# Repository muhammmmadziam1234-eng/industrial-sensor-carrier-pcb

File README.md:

# Meridian Industrial Sensor Carrier · Revision B

Meridian is a four-layer PCB design for integrating a 3.3 V controller with RS-485, SPI, I²C, analog sensing, and low-side loads. Revision B adds a hardware supply selector, wider power routes, dedicated inner copper planes, and an editable schematic and layout tied to the same pin map.

[View all four copper layers](media/four-layer-inspection.png)

| Deliverable | Contents |
| --- | --- |
| [KiCad project](cad/meridian-carrier.kicad_pro) | Native schematic, PCB, project symbol and footprint libraries, and explicit routing constraints. |
| [Schematic PDF](reports/meridian-schematic.pdf) | Review drawing organized by electrical function. |
| [AutoCAD DXF](cad/meridian-carrier.dxf) | Millimetre model with board outline, mounting, drills, individual tracks, and separately editable inner plane models. |
| [Mechanical STEP](cad/meridian-carrier-board.step) | Board solid for enclosure fit, with mounting bores checked against the nonplated drill output. |
| [Assembly and purchasing](cad/bill-of-materials.csv) | Reference designators, package details, candidate manufacturer part numbers, and source links. |
| [Connector and jumper map](design-review.md) | Controller pinout, field connectors, power selection, and test points. |
| [Engineering basis](engineering-basis.md) | Component and fabrication references, electrical decisions, and the integration envelope. |
| [Fabrication review](fab/README.md) | Stack, drill, copper, and manufacturing checks for the prototype package. |
| [First-article acceptance](first-article.md) | Bench setup, measurable acceptance criteria, and evidence to collect. |

The board measures 101.60 × 76.20 mm and uses four 3.20 mm mounting holes. L2 provides a ground plane and L3 provides the 3.3 V plane. The two outer layers carry signal and power tracks. JP3 selects the controller supply or a regulated auxiliary input with a single shunt.

## Verify and regenerate

Install the Python dependencies in [requirements.txt](requirements.txt). Run the generators from the project root in this order.

~~~sh
python schematic.py
python route.py
python verify.py
python check_verifier.py
python planes.py
python export_cad.py
python render_preview.py
~~~

[Geometry evidence](verification.json) covers the routed copper, hole spacing, board edge, and connectivity. [Plane evidence](plane-verification.json) covers continuous inner pours and their isolation envelopes. [Export evidence](cad/export-checks.json) records the DXF audit and KiCad geometry readback. [KiCad 10.0.8 results](reports/native-summary.json) record zero electrical or layout findings, zero unconnected items, zero schematic parity issues, and agreement on all 124 electrical pad assignments. The [fabrication export check](reports/fabrication-summary.json) confirms nine Gerber layers, 117 plated and four nonplated drill hits, and 23 top-side surface-mount placements. See [the fabrication folder](fab/README.md) for export instructions and the file manifest.

[Mechanical readback](reports/mechanical-summary.json) compares the STEP solid with the board dimensions and all four mounting bores in the nonplated drill output. The STEP is for fit review and excludes fitted components. Its exported Z span reflects the KiCad model. Use the fabricator-approved stack and component heights to set actual enclosure clearances.

This handoff is for engineering and prototype review. Fabrication approval requires final part-to-footprint confirmation and review of the chosen fab stack. Hardware validation uses the documented bring-up plan.

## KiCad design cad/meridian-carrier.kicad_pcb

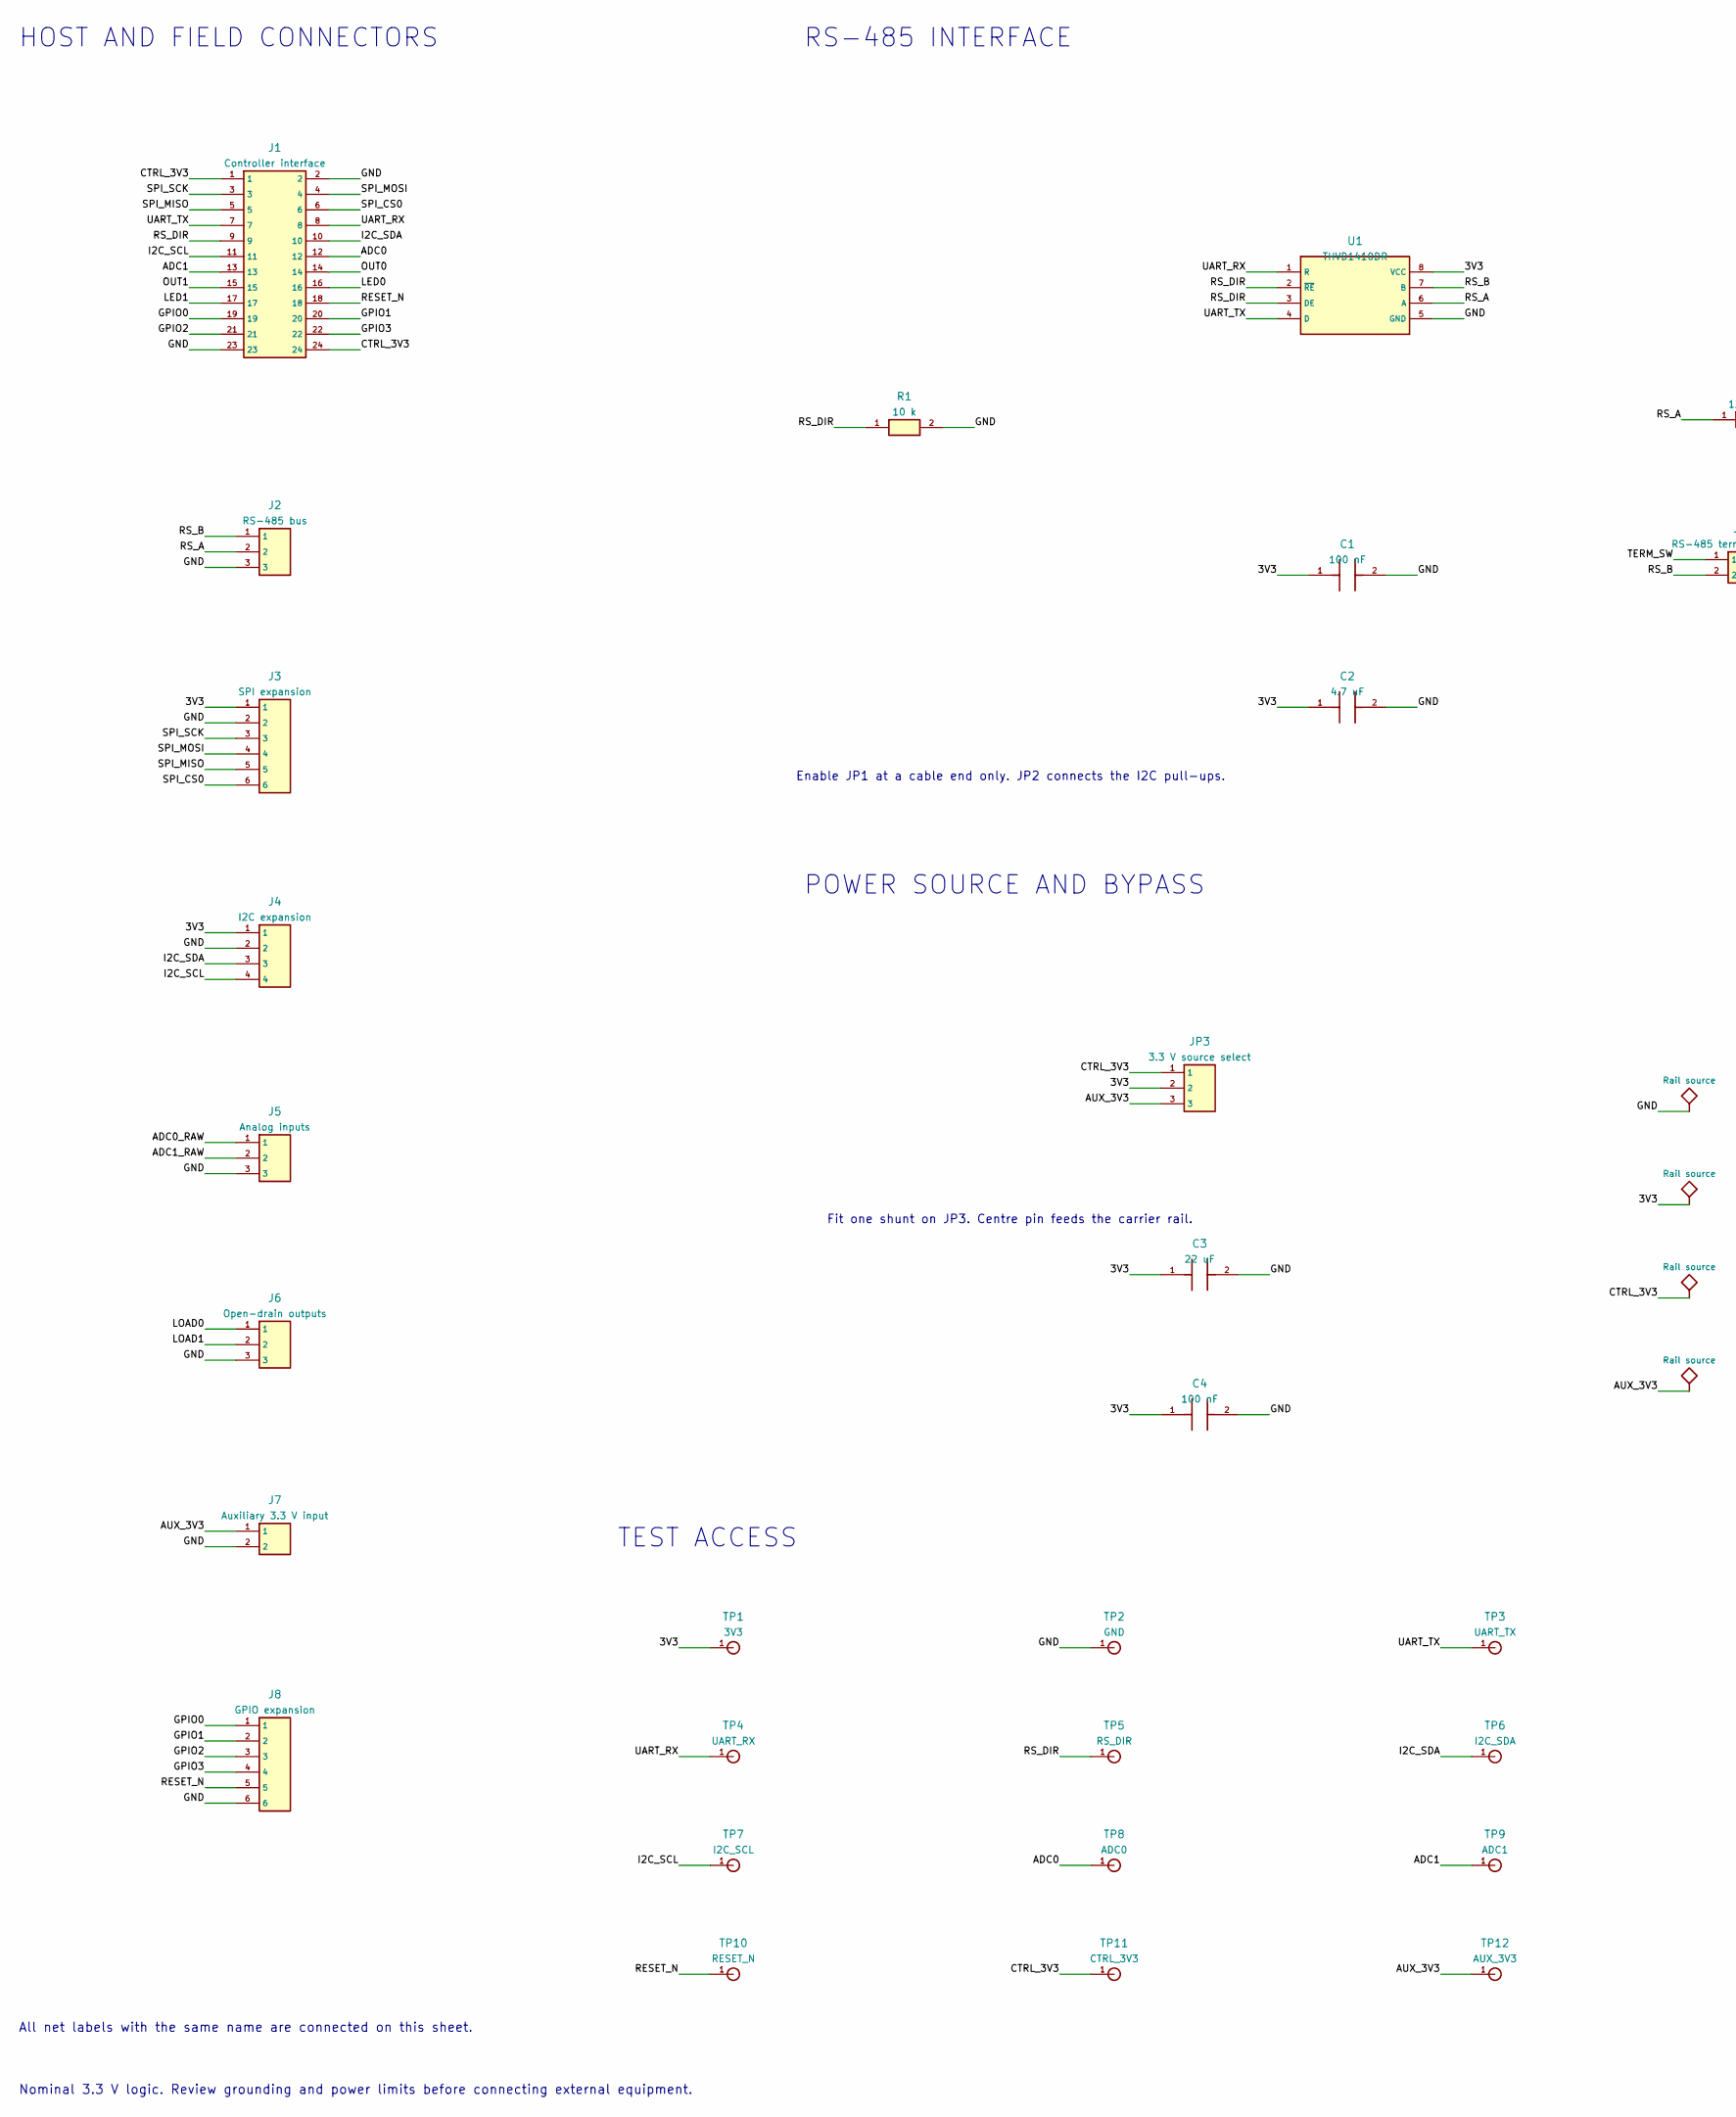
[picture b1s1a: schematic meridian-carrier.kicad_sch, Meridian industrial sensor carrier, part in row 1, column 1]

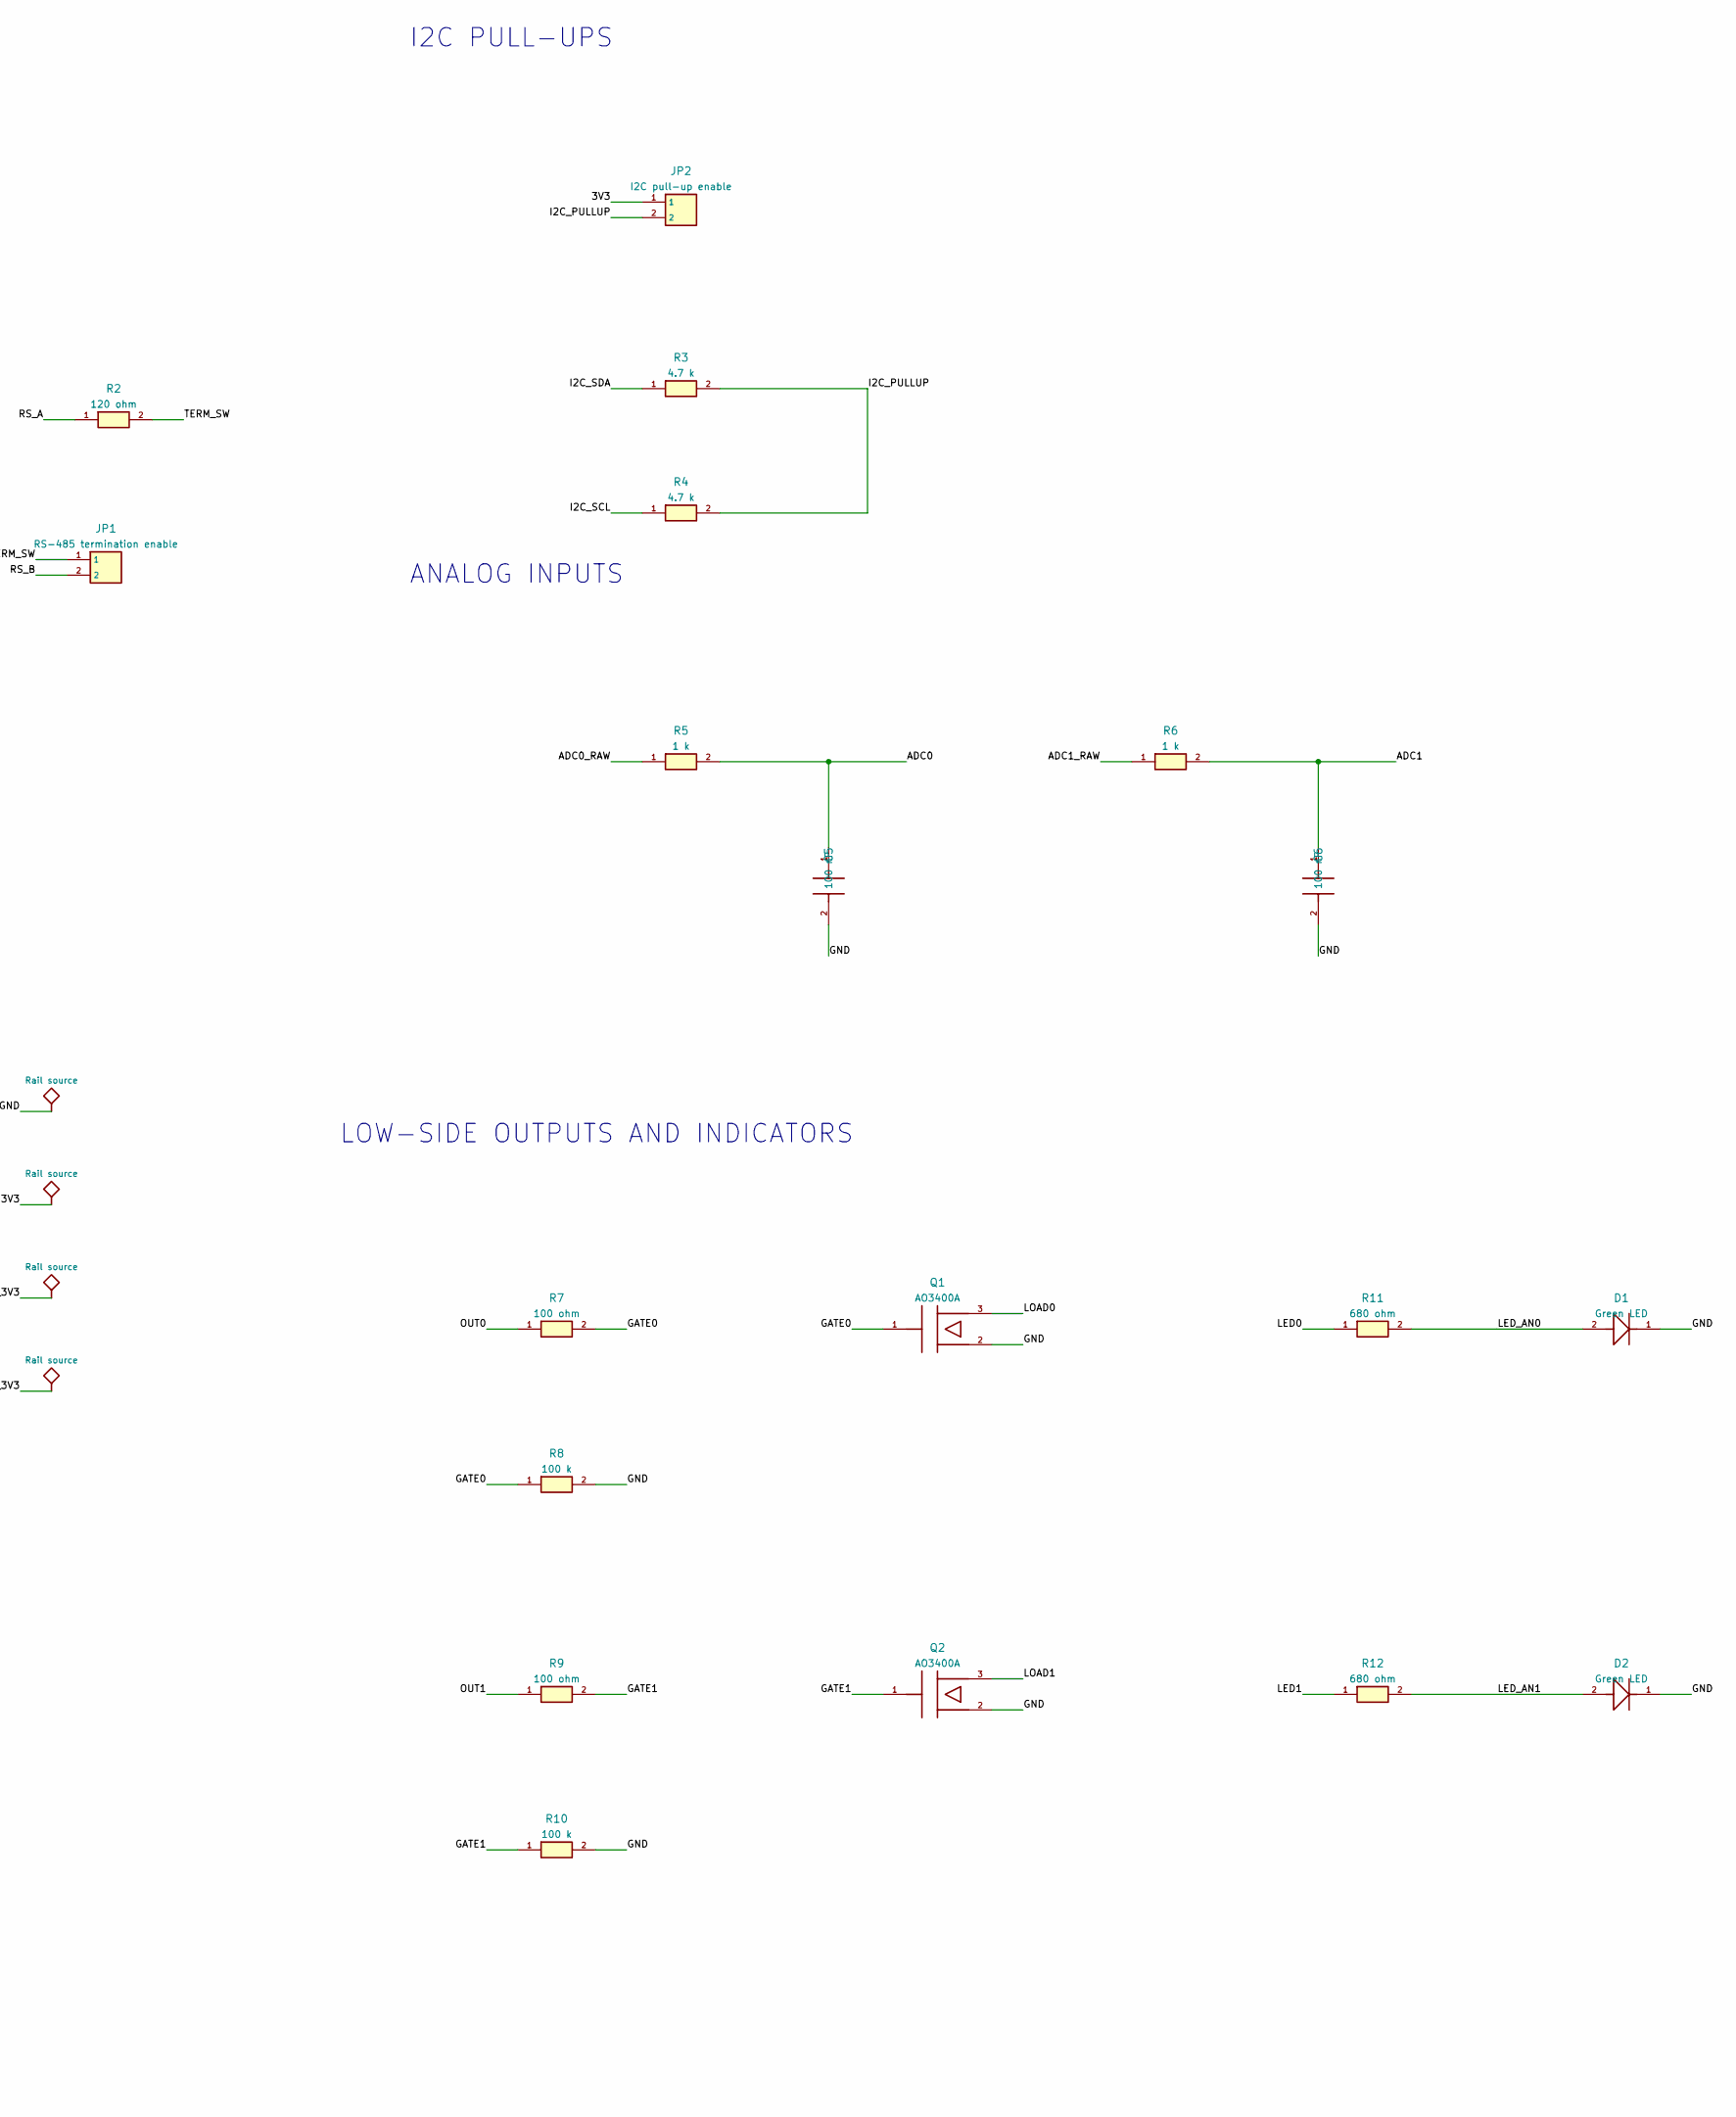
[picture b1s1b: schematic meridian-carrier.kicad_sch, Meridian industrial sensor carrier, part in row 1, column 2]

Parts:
C1, C4: 100 nF; Chip_0603_H
C2: 4.7 uF; Chip_0805_H
C3: 22 uF; Chip_0805_H
C5, C6: 100 nF; Chip_0603_V
D1, D2: Green LED; Chip_0603_H
J1: Controller interface; Header_2x12_P2p54mm
J2: RS-485 bus; Header_1x03_V_P2p54mm
J3: SPI expansion; Header_1x06_V_P2p54mm
J4: I2C expansion; Header_1x04_V_P2p54mm
J5: Analog inputs; Header_1x03_V_P2p54mm
J6: Open-drain outputs; Header_1x03_V_P2p54mm
J7: Auxiliary 3.3 V input; Header_1x02_V_P2p54mm
J8: GPIO expansion; Header_1x06_V_P2p54mm
JP1: RS-485 termination enable; Header_1x02_H_P2p54mm
JP2: I2C pull-up enable; Header_1x02_H_P2p54mm
JP3: 3.3 V source select; Header_1x03_H_P2p54mm
Q1, Q2: AO3400A; SOT_23
R1: 10 k; Chip_0603_H
R2: 120 ohm; Chip_0805_V
R3, R4: 4.7 k; Chip_0603_H
R5, R6: 1 k; Chip_0603_H
R7, R9: 100 ohm; Chip_0603_H
R8, R10: 100 k; Chip_0603_H
R11, R12: 680 ohm; Chip_0603_H
TP1: 3V3; TestLand_1p5mm
TP2: GND; TestLand_1p5mm
TP3: UART_TX; TestLand_1p5mm
TP4: UART_RX; TestLand_1p5mm
TP5: RS_DIR; TestLand_1p5mm
TP6: I2C_SDA; TestLand_1p5mm
TP7: I2C_SCL; TestLand_1p5mm
TP8: ADC0; TestLand_1p5mm
TP9: ADC1; TestLand_1p5mm
TP10: RESET_N; TestLand_1p5mm
TP11: CTRL_3V3; TestLand_1p5mm
TP12: AUX_3V3; TestLand_1p5mm
U1: THVD1410DR; SOIC_8_3p9x4p9mm

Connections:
/3V3: C1.1, C2.1, C3.1, C4.1, J3.1, J4.1, JP2.1, JP3.2, TP1.1, U1.8 (VCC)
/ADC0: C5.1, J1.12, R5.2, TP8.1
/ADC0_RAW: J5.1, R5.1
/ADC1: C6.1, J1.13, R6.2, TP9.1
/ADC1_RAW: J5.2, R6.1
/AUX_3V3: J7.1, JP3.3, TP12.1
/CTRL_3V3: J1.1, J1.24, JP3.1, TP11.1
/GATE0: Q1.1 (G), R7.2, R8.1
/GATE1: Q2.1 (G), R9.2, R10.1
/GND: C1.2, C2.2, C3.2, C4.2, C5.2, C6.2, D1.1, D2.1, J1.2, J1.23, J2.3, J3.2, J4.2, J5.3, J6.3, J7.2, J8.6, Q1.2 (S), Q2.2 (S), R1.2, R8.2, R10.2, TP2.1, U1.5 (GND)
/GPIO0: J1.19, J8.1
/GPIO1: J1.20, J8.2
/GPIO2: J1.21, J8.3
/GPIO3: J1.22, J8.4
/I2C_PULLUP: JP2.2, R3.2, R4.2
/I2C_SCL: J1.11, J4.4, R4.1, TP7.1
/I2C_SDA: J1.10, J4.3, R3.1, TP6.1
/LED0: J1.16, R11.1
/LED1: J1.17, R12.1
/LED_AN0: D1.2, R11.2
/LED_AN1: D2.2, R12.2
/LOAD0: J6.1, Q1.3 (D)
/LOAD1: J6.2, Q2.3 (D)
/OUT0: J1.14, R7.1
/OUT1: J1.15, R9.1
/RESET_N: J1.18, J8.5, TP10.1
/RS_A: J2.2, R2.1, U1.6 (A)
/RS_B: J2.1, JP1.2, U1.7 (B)
/RS_DIR: J1.9, R1.1, TP5.1, U1.2 (~RE), U1.3 (DE)
/SPI_CS0: J1.6, J3.6
/SPI_MISO: J1.5, J3.5
/SPI_MOSI: J1.4, J3.4
/SPI_SCK: J1.3, J3.3
/TERM_SW: JP1.1, R2.2
/UART_RX: J1.8, TP4.1, U1.1 (R)
/UART_TX: J1.7, TP3.1, U1.4 (D)

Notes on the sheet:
HOST AND FIELD CONNECTORS
RS-485 INTERFACE
POWER SOURCE AND BYPASS
TEST ACCESS
I2C PULL-UPS
ANALOG INPUTS
LOW-SIDE OUTPUTS AND INDICATORS
Fit one shunt on JP3. Centre pin feeds the carrier rail.
Enable JP1 at a cable end only. JP2 connects the I2C pull-ups.
All net labels with the same name are connected on this sheet.
Nominal 3.3 V logic. Review grounding and power limits before connecting external equipment.

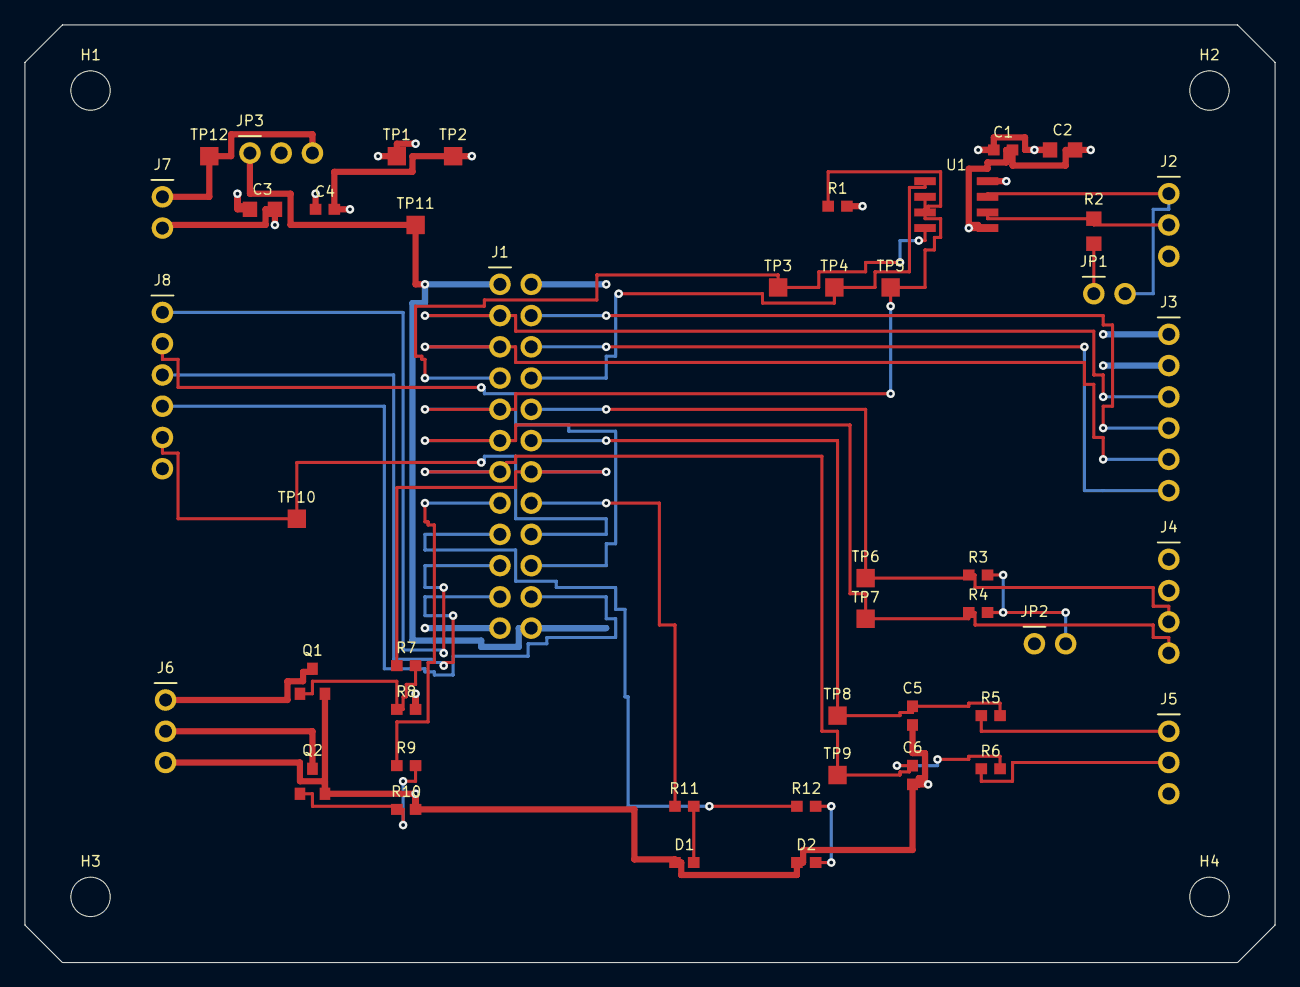
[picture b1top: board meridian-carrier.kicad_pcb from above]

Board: 4 copper layers, 101.6 x 76.2 mm, 50 parts (0 on the bottom side), 36 nets.

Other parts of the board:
H1, H2, H3, H4: Mount_M3

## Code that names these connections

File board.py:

"""Source netlist and component placement for the Meridian I/O carrier."""
from dataclasses import dataclass
from collections import defaultdict

GRID = 0.254
W, H = 400, 300
MOUNTING = [(21, 21), (379, 21), (21, 279), (379, 279)]
LAYER_NAMES = ("F.Cu", "In1.Cu", "In2.Cu", "B.Cu")
SIGNAL_WIDTH = .254
POWER_WIDTH = .508
POWER_NETS = frozenset({'3V3', 'CTRL_3V3', 'AUX_3V3', 'GND', 'LOAD0', 'LOAD1'})
PLANES = {1: 'GND', 2: '3V3'}


def track_width(net):
    return POWER_WIDTH if net in POWER_NETS else SIGNAL_WIDTH

CLEARANCE = .254
VIA_DIA = .70
VIA_DRILL = .30

@dataclass(frozen=True)
class Pad:
    ref: str
    pin: int
    net: str
    x: int
    y: int
    width: float
    height: float
    drill: float = 0

    @property
    def layers(self):
        return range(4) if self.drill else (0,)

@dataclass
class Part:
    ref: str
    value: str
    package: str
    x: int
    y: int
    pads: list

PARTS = []

def part(ref, value, package, x, y, specs, size, drill=0):
    pads = [Pad(ref, i + 1, net, x + dx, y + dy, *size, drill)
            for i, (dx, dy, net) in enumerate(specs)]
    PARTS.append(Part(ref, value, package, x, y, pads))

def header(ref, value, x, y, nets, horizontal=False):
    coords = [(10*i, 0, net) if horizontal else (0, 10*i, net)
              for i, net in enumerate(nets)]
    part(ref, value, f"2.54 mm 1x{len(nets)}", x, y, coords, (1.75, 1.75), 1.05)

def two(ref, value, package, x, y, a, b, vertical=False):
    pitch = 3 if package == "0603" else 4
    offsets = [(0, -pitch, a), (0, pitch, b)] if vertical else [(-pitch, 0, a), (pitch, 0, b)]
    size = (.95, .90) if package == "0603" else (1.18, 1.25)
    if vertical:
        size = size[::-1]
    part(ref, value, package, x, y, offsets, size)

controller = [
    "CTRL_3V3", "GND", "SPI_SCK", "SPI_MOSI", "SPI_MISO", "SPI_CS0",
    "UART_TX", "UART_RX", "RS_DIR", "I2C_SDA", "I2C_SCL", "ADC0",
    "ADC1", "OUT0", "OUT1", "LED0", "LED1", "RESET_N",
    "GPIO0", "GPIO1", "GPIO2", "GPIO3", "GND", "CTRL_3V3",
]
part("J1", "Controller interface", "2.54 mm 2x12", 152, 83,
     [(10*(i % 2), 10*(i//2), net) for i, net in enumerate(controller)],
     (1.75, 1.75), 1.05)

header("J2", "RS-485 bus", 366, 54, ["RS_B", "RS_A", "GND"])
header("J3", "SPI expansion", 366, 99, ["3V3", "GND", "SPI_SCK", "SPI_MOSI", "SPI_MISO", "SPI_CS0"])
header("J4", "I2C expansion", 366, 171, ["3V3", "GND", "I2C_SDA", "I2C_SCL"])
header("J5", "Analog inputs", 366, 226, ["ADC0_RAW", "ADC1_RAW", "GND"])
header("J6", "Open-drain outputs", 45, 216, ["LOAD0", "LOAD1", "GND"])
header("J7", "Auxiliary 3.3 V input", 44, 55, ["AUX_3V3", "GND"])
header("J8", "GPIO expansion", 44, 92, ["GPIO0", "GPIO1", "GPIO2", "GPIO3", "RESET_N", "GND"])
header("JP1", "RS-485 termination enable", 342, 86, ["TERM_SW", "RS_B"], True)
header("JP2", "I2C pull-up enable", 323, 198, ["3V3", "I2C_PULLUP"], True)
header("JP3", "3.3 V source select", 72, 41, ["CTRL_3V3", "3V3", "AUX_3V3"], True)

part("U1", "THVD1410DR", "SOIC-8 3.9 mm", 298, 58,
     [(-10, -8, "UART_RX"), (-10, -3, "RS_DIR"), (-10, 2, "RS_DIR"), (-10, 7, "UART_TX"),
      (10, 7, "GND"), (10, 2, "RS_A"), (10, -3, "RS_B"), (10, -8, "3V3")],
     (1.76, .65))
two("R1", "10 k", "0603", 260, 58, "RS_DIR", "GND")
two("R2", "120 ohm", "0805", 342, 66, "RS_A", "TERM_SW", True)
two("C1", "100 nF", "0603", 313, 40, "3V3", "GND")
two("C2", "4.7 uF", "0805", 332, 40, "3V3", "GND")
two("C3", "22 uF", "0805", 76, 59, "3V3", "GND")
two("C4", "100 nF", "0603", 96, 59, "3V3", "GND")
two("R3", "4.7 k", "0603", 305, 176, "I2C_SDA", "I2C_PULLUP")
two("R4", "4.7 k", "0603", 305, 188, "I2C_SCL", "I2C_PULLUP")
two("R5", "1 k", "0603", 309, 221, "ADC0_RAW", "ADC0")
two("R6", "1 k", "0603", 309, 238, "ADC1_RAW", "ADC1")
two("C5", "100 nF", "0603", 284, 221, "ADC0", "GND", True)
two("C6", "100 nF", "0603", 284, 240, "ADC1", "GND", True)

for i, y in enumerate((210, 242)):
    gate = f"GATE{i}"
    part(f"Q{i+1}", "AO3400A", "SOT-23", 92, y,
         [(-4, 4, gate), (4, 4, "GND"), (0, -4, f"LOAD{i}")], (.87, 1.00))
    two(f"R{7 + i*2}", "100 ohm", "0603", 122, y - 5, f"OUT{i}", gate)
    two(f"R{8 + i*2}", "100 k", "0603", 122, y + 9, gate, "GND")
    two(f"R{11 + i}", "680 ohm", "0603", 211 + 39*i, 250, f"LED{i}", f"LED_AN{i}")
    two(f"D{i+1}", "Green LED", "0603", 211 + 39*i, 268, "GND", f"LED_AN{i}")

for i, (net, x, y) in enumerate([
    ("3V3", 119, 42), ("GND", 137, 42), ("UART_TX", 241, 84),
    ("UART_RX", 259, 84), ("RS_DIR", 277, 84), ("I2C_SDA", 269, 177),
    ("I2C_SCL", 269, 190), ("ADC0", 260, 221), ("ADC1", 260, 240),
    ("RESET_N", 87, 158), ("CTRL_3V3", 125, 64), ("AUX_3V3", 59, 42),
], 1):
    part(f"TP{i}", net, "1.5 mm test land", x, y, [(0, 0, net)], (1.5, 1.5))

PADS = [pad for item in PARTS for pad in item.pads]
NETS = defaultdict(list)
for pad in PADS:
    NETS[pad.net].append(pad)

if __name__ == "__main__":
    print(f"{len(PARTS)} footprints, {len(PADS)} pads, {len(NETS)} nets")
    print("Nets with fewer than two pads:", [net for net, pads in NETS.items() if len(pads) < 2])
